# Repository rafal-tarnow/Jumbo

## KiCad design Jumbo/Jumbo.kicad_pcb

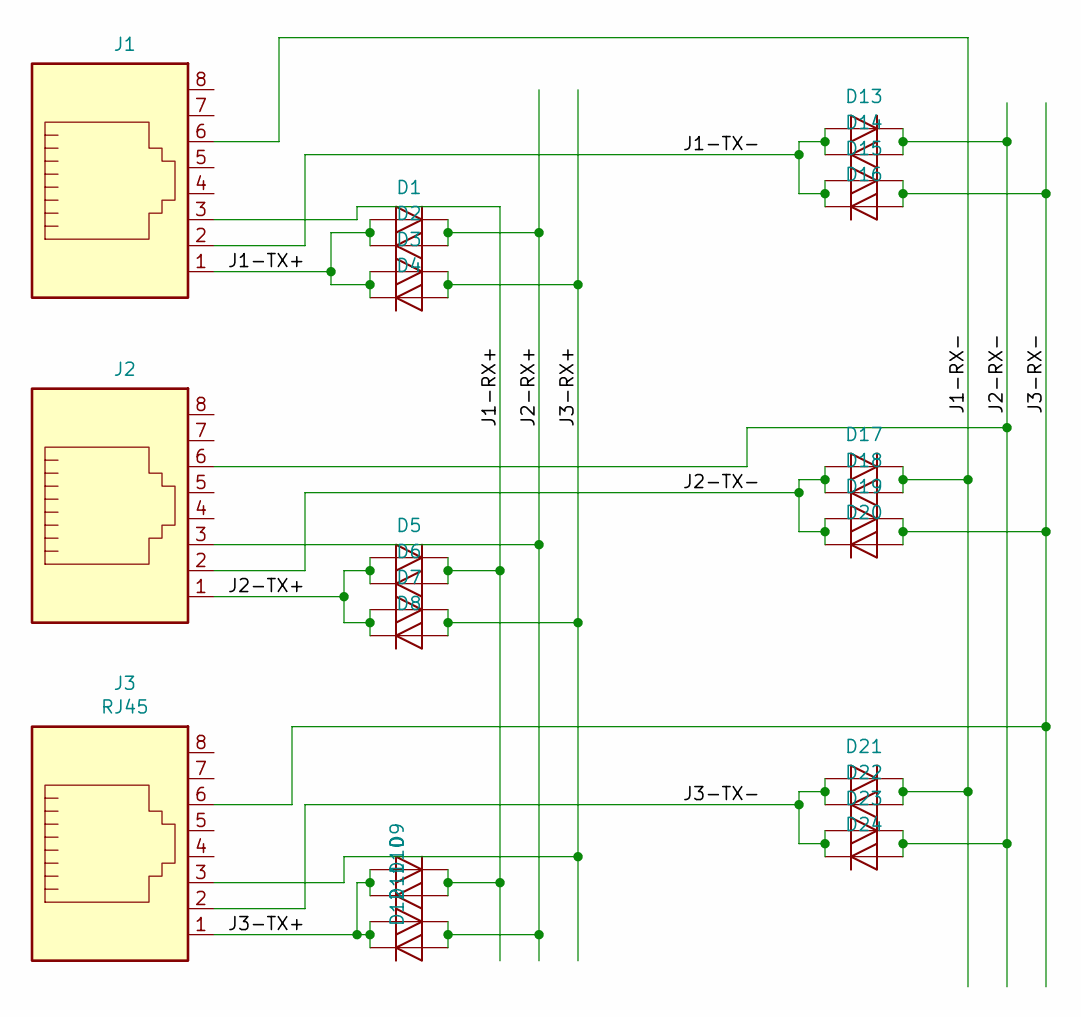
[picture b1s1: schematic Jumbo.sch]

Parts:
D1, D2, D3, D4, D5, D6, D7, D8, D9, D10, D11, D12, D13, D14, D15, D16, D17, D18, D19, D20, D21, D22, D23, D24: BA243; D_DO-35_SOD27_P7.62mm_Horizontal
J1, J2, J3: RJ45; RJ45GE

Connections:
/J1-RX+: D5.1 (K), D6.2 (A), D9.1 (K), D10.2 (A), J1.3
/J1-RX-: D17.1 (K), D18.2 (A), D21.1 (K), D22.2 (A), J1.6
/J1-TX+: D1.2 (A), D2.1 (K), D3.2 (A), D4.1 (K), J1.1
/J1-TX-: D13.2 (A), D14.1 (K), D15.2 (A), D16.1 (K), J1.2
/J2-RX+: D1.1 (K), D2.2 (A), D11.1 (K), D12.2 (A), J2.3
/J2-RX-: D13.1 (K), D14.2 (A), D23.1 (K), D24.2 (A), J2.6
/J2-TX+: D5.2 (A), D6.1 (K), D7.2 (A), D8.1 (K), J2.1
/J2-TX-: D17.2 (A), D18.1 (K), D19.2 (A), D20.1 (K), J2.2
/J3-RX+: D3.1 (K), D4.2 (A), D7.1 (K), D8.2 (A), J3.3
/J3-RX-: D15.1 (K), D16.2 (A), D19.1 (K), D20.2 (A), J3.6
/J3-TX+: D9.2 (A), D10.1 (K), D11.2 (A), D12.1 (K), J3.1
/J3-TX-: D21.2 (A), D22.1 (K), D23.2 (A), D24.1 (K), J3.2

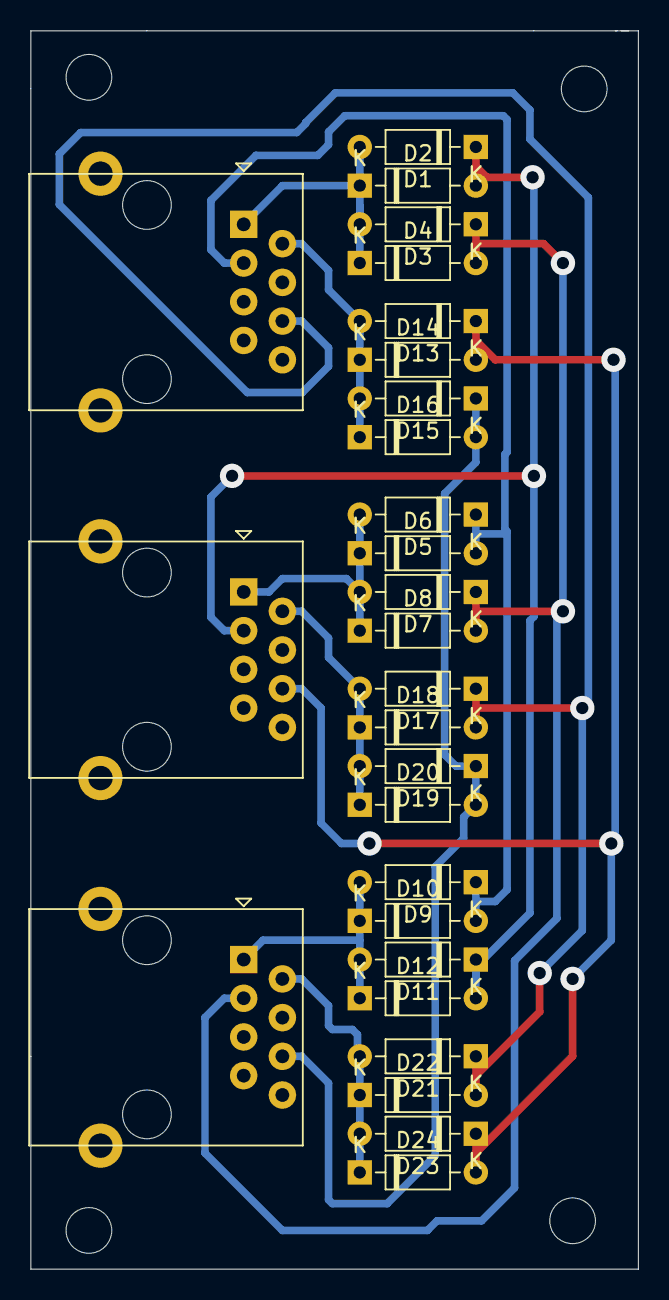
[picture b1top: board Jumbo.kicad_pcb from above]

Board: 2 copper layers, 39.9 x 81.3 mm, 27 parts (0 on the bottom side), 12 nets.
